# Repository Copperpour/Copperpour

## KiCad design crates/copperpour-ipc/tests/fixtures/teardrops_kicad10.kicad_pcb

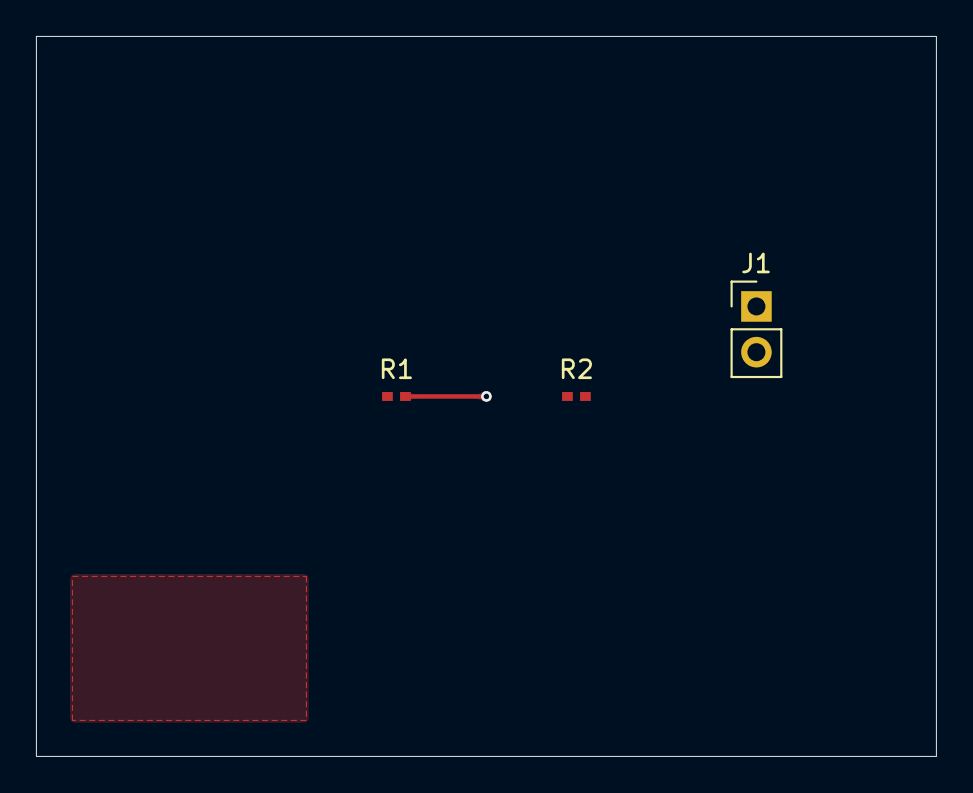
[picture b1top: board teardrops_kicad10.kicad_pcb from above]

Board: 4 copper layers, 50.0 x 40.0 mm, 3 parts (0 on the bottom side), 2 nets.

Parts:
J1: PinHeader_1x02_P2.54mm_Vertical
R1: 10k; R_0402
R2: 4.7k; R_0402

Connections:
GND: J1.2, R1.2, R2.1
VCC: J1.1, R1.1, R2.2
